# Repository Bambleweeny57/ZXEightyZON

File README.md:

# ZXEightyZON 🎶

**ZXEightyZON** is a new sound interface for the ZX81, built around the **YM2149F** or **AY-3-8910** sound chips. 
Designed as a timing-accurate ZON-compatible sound card, this board offers clean integration with existing ZON-X81 and ZON-X demos and playback routines, while introducing flexible channel mixing options for stereo output.

---

## 🔧 Key Features

- **Sound Chip**: YM2149F or AY-3-8910
- **Address Decoding**:  
  Generic 8-bit address decoding via GAL logic, supporting all 4 known ZON-X register and data address combinations:
  - Latch: `0xDF`, Data: `0x0F` → Modified ZON-X  
  - Latch: `0xCF`, Data: `0x1F` → Original ZON-X  
  - Latch: `0xCF`, Data: `0x0F` → From ZON-X user manual  
  - Latch: `0xDF`, Data: `0x1F` → Additional combination
- **Stereo Output Configuration**:
  - Channel A: Always routed to **Left**
  - Mixed Channel: Selectable via jumper—either **Channel B** or **Channel C**
  - Right Channel: Assigned to the **non-mixed** channel  
    - If **B is mixed**, then **C is Right**  
    - If **C is mixed**, then **B is Right**
- **Noise Channel Nomination**:
  - Jumper-based selection of B or C as the mixed/noise channel
  - Supports regional playback preferences:
    - Western demos typically mix **Channel B**
    - Eastern demos often mix **Channel C**
- **Master Clock Selection**:
  - Jumper-based selection for either bus clock or divided-by-2 clock
  - `CLK_OUT`: Buffered ZX81 bus clock (YM2149 SEL = GND)
  - `CLK_DIV2`: Internally divided clock (YM2149 SEL = !GND or AY-3-8910)
- **PSG Clock Divider Control**:
  - Jumper-based selection for whether PSG divides master clock (YM2149) or receives pre-divided clock
  - **Closed**: Connect YM2149 SEL to GND (PSG divides clock - use with YM2149 only)
  - **Open**: Disconnect SEL from GND (PSG uses divided clock - use with YM2149 or AY-3-8910)

---

## 📌 Pin Assignments (GAL22V10)

| Pin | Signal     | Description                          |
|-----|------------|--------------------------------------|
| 01  | CLK_IN     | Input clock                          |
| 02  | A0         | Address bit 0                        |
| 03  | A1         | Address bit 1                        |
| 04  | A2         | Address bit 2                        |
| 05  | A3         | Address bit 3                        |
| 06  | A4         | Address bit 4                        |
| 07  | A5         | Address bit 5                        |
| 08  | A6         | Address bit 6                        |
| 09  | A7         | Address bit 7                        |
| 10  | !WR_N      | Active-low write signal              |
| 11  | !IORQ_N    | Active-low I/O request               |
| 12  | GND        | Ground                               |
| 13  | !RD_N      | Active-low read signal               |
| 14  | BDIR       | PSG control: data direction          |
| 15  | BC1        | PSG control: register/data select    |
| 16  | CLK_DIV2   | Divided clock output (toggle logic)  |
| 17  | CLK_OUT    | Clock Buffered passthrough           |
| 18  | NC         | Not connected routed to header       |
| 19  | NC         | Not connected routed to header       |
| 20  | NC         | Not connected routed to header       |
| 21  | NC         | Not connected routed to header       |
| 22  | NC         | Not connected routed to header       |
| 23  | NC         | Not connected routed to header       |
| 24  | VCC        | Power                                |

---

### 🧮 ZXEightyZON Truth Table – ZON-X Address Variants vs PSG Control Signals

This table maps decoded ZON-X addresses and I/O control signals to PSG control outputs. 
Each variant is listed explicitly to reflect all known ZON-X mappings.

| Variant                  | /IORQ | /WR  | Address | Operation     | BDIR | BC1 |
|--------------------------|:-----:|:----:|:-------:|:--------------|:----:|:---:|
| Modified ZON-X           | Low   | Low  | 0xDF    | Latch         | 1    | 1   |
| Modified ZON-X           | Low   | Low  | 0x0F    | Data Write    | 1    | 0   |
| Original ZON-X           | Low   | Low  | 0xCF    | Latch         | 1    | 1   |
| Original ZON-X           | Low   | Low  | 0x1F    | Data Write    | 1    | 0   |
| Manual Variant           | Low   | Low  | 0xCF    | Latch         | 1    | 1   |
| Manual Variant           | Low   | Low  | 0x0F    | Data Write    | 1    | 0   |
| Additional Combination   | Low   | Low  | 0xDF    | Latch         | 1    | 1   |
| Additional Combination   | Low   | Low  | 0x1F    | Data Write    | 1    | 0   |
| —                        | Any   | Any  | —       | No Operation  | 0    | 0   |

**Notes:**
- `BDIR` and `BC1` follow PSG truth table conventions for register and data access.
- Address variants are duplicated intentionally to reflect ZON-X lineage and contributor clarity.
- This logic ensures compatibility with Sinclair-era demos and hardware, while supporting AY-ZONIC extensions.

 **Note on `RD` Signal Decoding:**  
> The `RD` line is actively decoded in ZXEightyZON’s GAL logic for completeness and future compatibility. While no current ZON-X compatible software or demos utilize `RD`, its inclusion ensures accurate bus semantics and allows for potential future expansions (e.g., memory-mapped reads or refined timing control). Builders can treat it as provisioned but dormant — present in logic, unused in practice.

---

## 🎚️ AY Channel Assignment Jumper Block

This 2×2 jumper block allows manual swapping of **AY channels B and C** between:

- **CH_B** → Mixed (Left + Right)
- **CH_C** → Right-only

**CH_A is always fixed to Left-only.**

---

### 📐 Pinout Grid

```
╭────────────┬────────────╮
│ [1] B_OUT  │ [2] CH_C   │
├────────────┼────────────┤
│ [3] CH_B   │ [4] C_OUT  │
╰────────────┴────────────╯
```

---

### 🔁 Jumper Combinations

- **Vertical jumpers**  
  - B_OUT → CH_B → Mixed (L+R)  
  - C_OUT → CH_C → Right-only  

- **Horizontal jumpers**  
  - B_OUT → CH_C → Right-only  
  - C_OUT → CH_B → Mixed (L+R)  

---

### 🧠 Notes

- CH_A is always Left-only  
- CH_B feeds Left + Right  
- CH_C feeds Right-only

> Vertical jumpers = B mixed, C right (Western demos)
> Horizontal jumpers = C mixed, B right (Eastern demos)

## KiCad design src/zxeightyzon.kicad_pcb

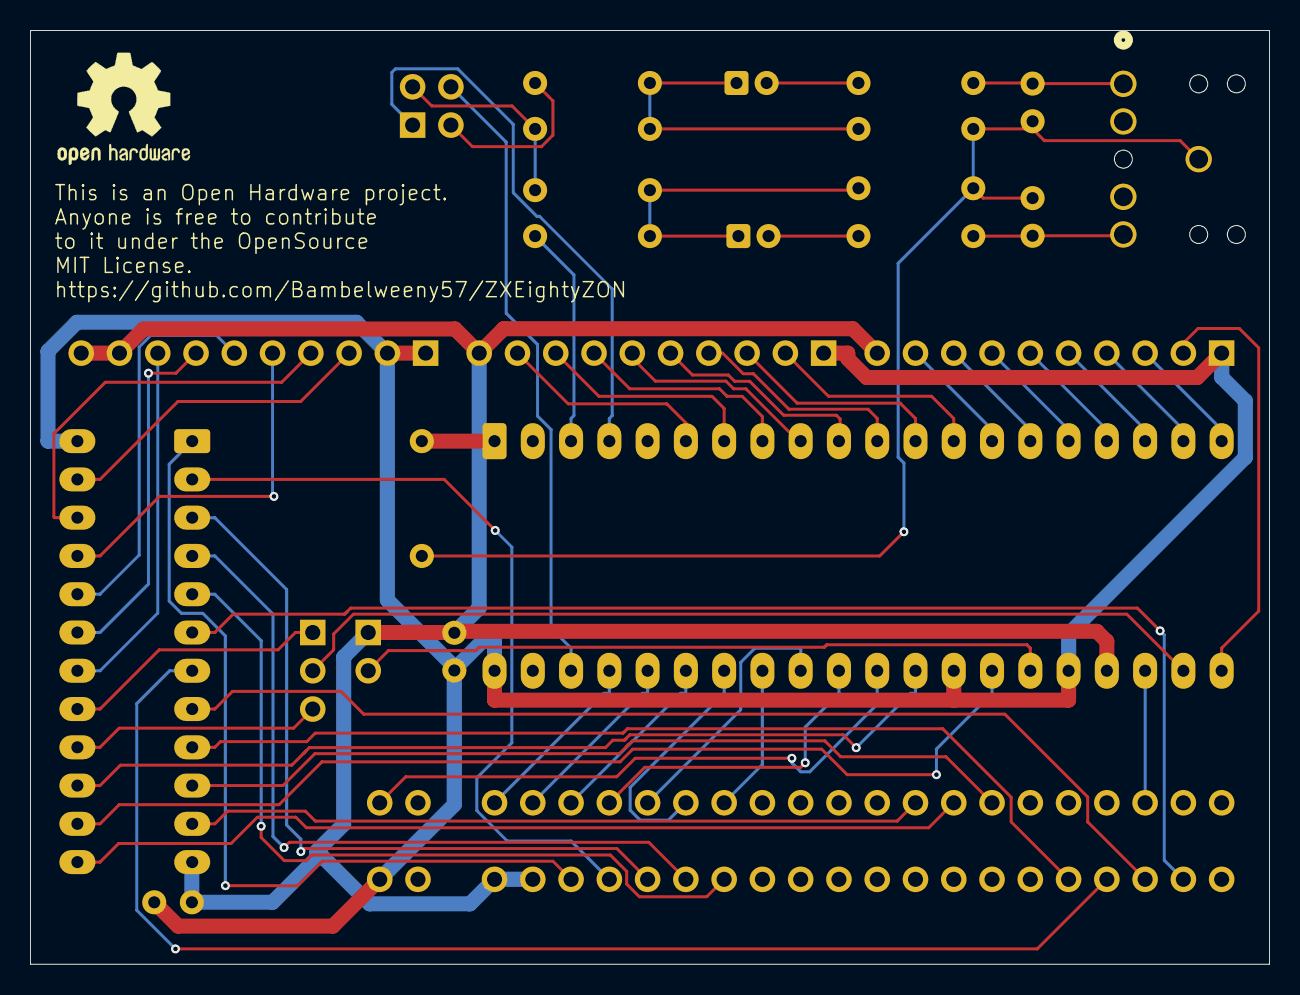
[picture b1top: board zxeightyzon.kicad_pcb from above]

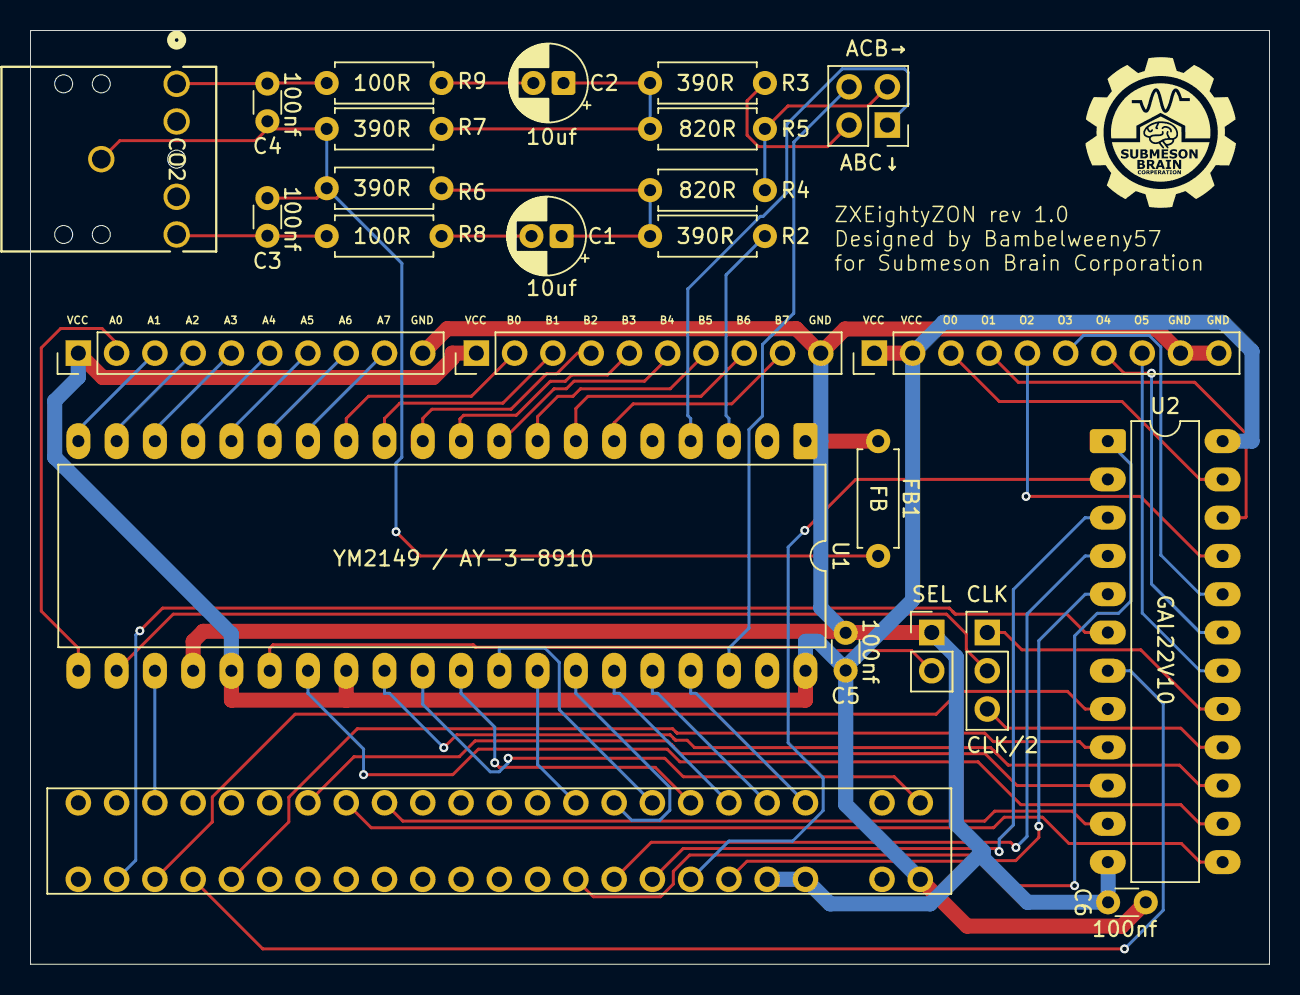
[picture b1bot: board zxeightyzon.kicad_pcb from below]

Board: 2 copper layers, 82.2 x 62.0 mm, 25 parts (24 on the bottom side), 63 nets.

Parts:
ABC↓: Conn_02x02_Top_Bottom; PinHeader_2x02_P2.54mm_Vertical
C1, C2: 10uf; CP_Radial_D5.0mm_P2.00mm
C3, C4, C5, C6: 100nf; C_Disc_D3.0mm_W1.6mm_P2.50mm
CLK: CLK Select; PinHeader_1x03_P2.54mm_Vertical
CO1: Connector ZX81; ZX81_EdgeConnector
CO2: LINEOUT; CONN5_SPC21348_MTC
FB1: FB; R_Axial_DIN0207_L6.3mm_D2.5mm_P7.62mm_Horizontal
J1 I/O-A, J2 I/O-B, J3 GAL: 01x10; PinHeader_1x10_P2.54mm_Vertical
R2, R3, R6, R7: 390R; R_Axial_DIN0207_L6.3mm_D2.5mm_P7.62mm_Horizontal
R4, R5: 820R; R_Axial_DIN0207_L6.3mm_D2.5mm_P7.62mm_Horizontal
R8, R9: 100R; R_Axial_DIN0207_L6.3mm_D2.5mm_P7.62mm_Horizontal
SEL: YM 1/2 CLK; PinHeader_1x02_P2.54mm_Vertical
U1: YM2149; DIP-40_W15.24mm_LongPads
U2: GAL22V10; DIP-24_W7.62mm_LongPads

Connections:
/A0: CO1.A9 (A0), U2.2 (I1)
/A1: CO1.A10 (A1), U2.3 (I2)
/A2: CO1.A11 (A2), U2.4 (I3)
/A3: CO1.A12 (A3), U2.5 (I4)
/A4: CO1.A24 (A4), U2.6 (I5)
/A5: CO1.A23 (A5), U2.8 (I7)
/A6: CO1.A22 (A6), U2.7 (I6)
/A7: CO1.A21 (A7), U2.9 (I8)
/A_OUT: R2.1, U1.3 (A)
/BC1: U1.29 (BC1), U2.15 (O8)
/BDIR: U1.27 (BDIR), U2.14 (O9)
/B_OUT: ABC↓.1, U1.4 (B)
/CLK: CO1.A8 (CLK), U2.1 (I0/CLK)
/CLK_DIV2: CLK.3 (B), U2.16 (O7)
/CLK_OUT: CLK.1 (A), U2.17 (O6)
/C_OUT: ABC↓.4, U1.38 (C)
/D0: CO1.B6 (D0), U1.37 (DA0)
/D1: CO1.B7 (D1), U1.36 (DA1)
/D2: CO1.B8 (D2), U1.35 (DA2)
/D3: CO1.B11 (D3), U1.34 (DA3)
/D4: CO1.B12 (D4), U1.33 (DA4)
/D5: CO1.B10 (D5), U1.32 (DA5)
/D6: CO1.B9 (D6), U1.31 (DA6)
/D7: CO1.B3 (D7), U1.30 (DA7)
/IOA0: J1 I/O-A.2, U1.21 (IOA0)
/IOA1: J1 I/O-A.3, U1.20 (IOA1)
/IOA2: J1 I/O-A.4, U1.19 (IOA2)
/IOA3: J1 I/O-A.5, U1.18 (IOA3)
/IOA4: J1 I/O-A.6, U1.17 (IOA4)
/IOA5: J1 I/O-A.7, U1.16 (IOA5)
/IOA6: J1 I/O-A.8, U1.15 (IOA6)
/IOA7: J1 I/O-A.9, U1.14 (IOA7)
/IOB0: J2 I/O-B.2, U1.13 (IOB0)
/IOB1: J2 I/O-B.3, U1.12 (IOB1)
/IOB2: J2 I/O-B.4, U1.11 (IOB2)
/IOB3: J2 I/O-B.5, U1.10 (IOB3)
/IOB4: J2 I/O-B.6, U1.9 (IOB4)
/IOB5: J2 I/O-B.7, U1.8 (IOB5)
/IOB6: J2 I/O-B.8, U1.7 (IOB6)
/IOB7: J2 I/O-B.9, U1.6 (IOB7)
/LEFT: C3.1, CO2.4, R8.2
/O0: J3 GAL.3, U2.23 (O0)
/O1: J3 GAL.4, U2.22 (O1)
/O2: J3 GAL.5, U2.21 (O2)
/O3: J3 GAL.6, U2.20 (O3)
/O4: J3 GAL.7, U2.19 (O4)
/O5: J3 GAL.8, U2.18 (O5)
/RIGHT: C4.1, CO2.1, R9.2
/~IOREQ: CO1.B17 (~IOREQ), U2.11 (I10)
/~RD: CO1.B18 (~RD), U2.13 (I11)
/~RESET: CO1.B23 (~RESET), U1.23 (~RESET)
/~WR: CO1.B19 (~WR), U2.10 (I9)
GND: C5.2, C6.2, CO1.A6 (GND), CO1.A7 (GND), FB1.1, J1 I/O-A.10, J2 I/O-B.10, J3 GAL.9, J3 GAL.10, SEL.1 (A), U1.1 (VSS), U1.24 (~A9), U2.12 (GND)
GND_AUDIO: C3.2, C4.2, CO2.5, FB1.2, R6.2, R7.2
unnamed: C1.1, R2.2, R4.1, R6.1
unnamed: C1.2, R8.1
unnamed: C2.1, R3.2, R5.1, R7.1
unnamed: C2.2, R9.1
unnamed: ABC↓.2, R3.1
unnamed: ABC↓.3, R4.2, R5.2
unnamed: SEL.2 (B), U1.26 (~SEL)
unnamed: CLK.2 (C), U1.22 (CLOCK)
VCC: C5.1, C6.1, CO1.A3 (+5Vcc), J1 I/O-A.1, J2 I/O-B.1, J3 GAL.1, J3 GAL.2, U1.25 (A8), U1.28 (BC2), U1.40 (VCC), U2.24 (VCC)

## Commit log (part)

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2025-10-19 initial gal commit
2025-10-19 inital schematic commit
2025-10-19 renamed branch
2025-10-19 updated gal readme
2025-10-20 update gal
2025-10-22 fixed CUPL issues in rev 1.0
2025-10-22 rebuilt gal
2025-10-22 rebuild
2025-10-22 change clock divider and added clock pass through
2025-10-23 Created Logos
2025-10-23 added clock passthrough
2025-10-23 update gal readme
2025-10-26 updated readme's and tried to get vs cupl to work, but not having it or im not understanding it.
2025-10-26 changed pin assignmant for clocks
2025-10-26 updated pin assignments to put unused ouputs at the top end
2025-10-26 added truth table to the cupl
2025-10-26 updated readme truth table
2025-10-26 change schematic to 22v10 and added outline base for pCB
2025-10-26 started schematic
2025-10-26 added logo footprint
2025-10-27 updated cupl to make it compile on the right drive
2025-10-27 added notes re RD.
2025-10-27 update vs code workspace
2025-10-27 updated readme's
2025-10-31 started PCB layout
2025-11-20 fab files
2026-01-04 updated CUPL
2026-01-04 Updated CUPL for PIN name
2026-01-04 update CUPL tab
2026-01-04 CUPL now working and the ZON is singing
2026-01-04 commented CUPL and addedd detail to the readme.md files
2026-01-04 images and a video added
2026-01-04 removed images
2026-01-04 added photos
2026-01-04 added png images
2026-01-04 updated the schematic pdf
2026-01-06 Added silkscreen overlays
2026-01-21 Added Open Hardware Silk Screen
2026-01-21 Exported STEP Model and added FreeCad project to create an enclosure.
2026-01-21 combined edge connector in to one solid in FreeCad project.
2026-01-21 Added IO Silk Screen Overlay
2026-01-21 Re rooted IO A
2026-01-21 new fab files

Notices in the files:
src/zxeightyzon.kicad_pcb:
MIT License.
